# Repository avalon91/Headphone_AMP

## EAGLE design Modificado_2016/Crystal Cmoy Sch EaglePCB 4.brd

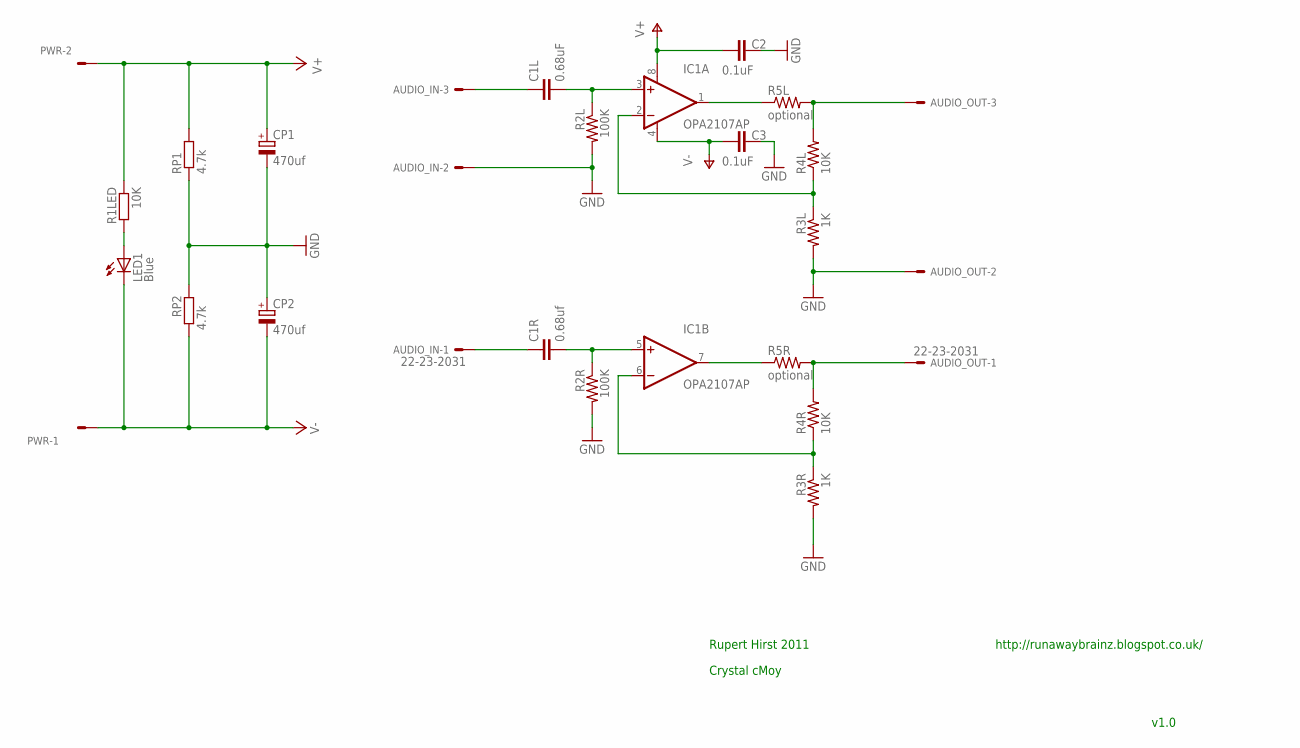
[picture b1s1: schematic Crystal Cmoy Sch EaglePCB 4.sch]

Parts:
AUDIO_IN: 22-23-2031
AUDIO_OUT: 22-23-2031
C1L: 0.68uF; C15B7
C1R: 0.68uf; C15B7
C2: 0.1uF; C5B2.5
C3: 0.1uF; C5B5.5
CP1, CP2: 470uf; E5-13
IC1: OPA2107AP; DIL08
LED1: Blue; LED3MM
PWR: 22-23-2021
R1LED: 10K; 0207/2V
R2L, R2R: 100K; 0207/10
R3L, R3R: 1K; 0207/10
R4L, R4R: 10K; 0207/10
R5L, R5R: optional; 0207/10
RP1, RP2: 4.7k; 0207/10

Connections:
GND: AUDIO_IN.2, AUDIO_OUT.2, C2.1, C3.2, CP1.-, CP2.+, R2L.2, R2R.2, R3L.2, R3R.2, RP1.1, RP2.2
L-IN: AUDIO_IN.3, C1L.1
L-OUT: AUDIO_OUT.3, R4L.2, R5L.2
unnamed: IC1.1 (OUT), R5L.1
unnamed: IC1.2 (-IN), R3L.1, R4L.1
unnamed: C1L.2, IC1.3 (+IN), R2L.1
unnamed: IC1.7 (OUT), R5R.1
unnamed: IC1.6 (-IN), R3R.1, R4R.1
unnamed: C1R.2, IC1.5 (+IN), R2R.1
unnamed: LED1.A, R1LED.2
R-IN: AUDIO_IN.1, C1R.1
R-OUT: AUDIO_OUT.1, R4R.2, R5R.2
V+: C2.2, CP1.+, IC1.8 (V+), PWR.2, R1LED.1, RP1.2
V-: C3.1, CP2.-, IC1.4 (V-), LED1.K (C), PWR.1, RP2.1

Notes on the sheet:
Rupert Hirst 2011
http://runawaybrainz.blogspot.co.uk/
Crystal cMoy
v1.0

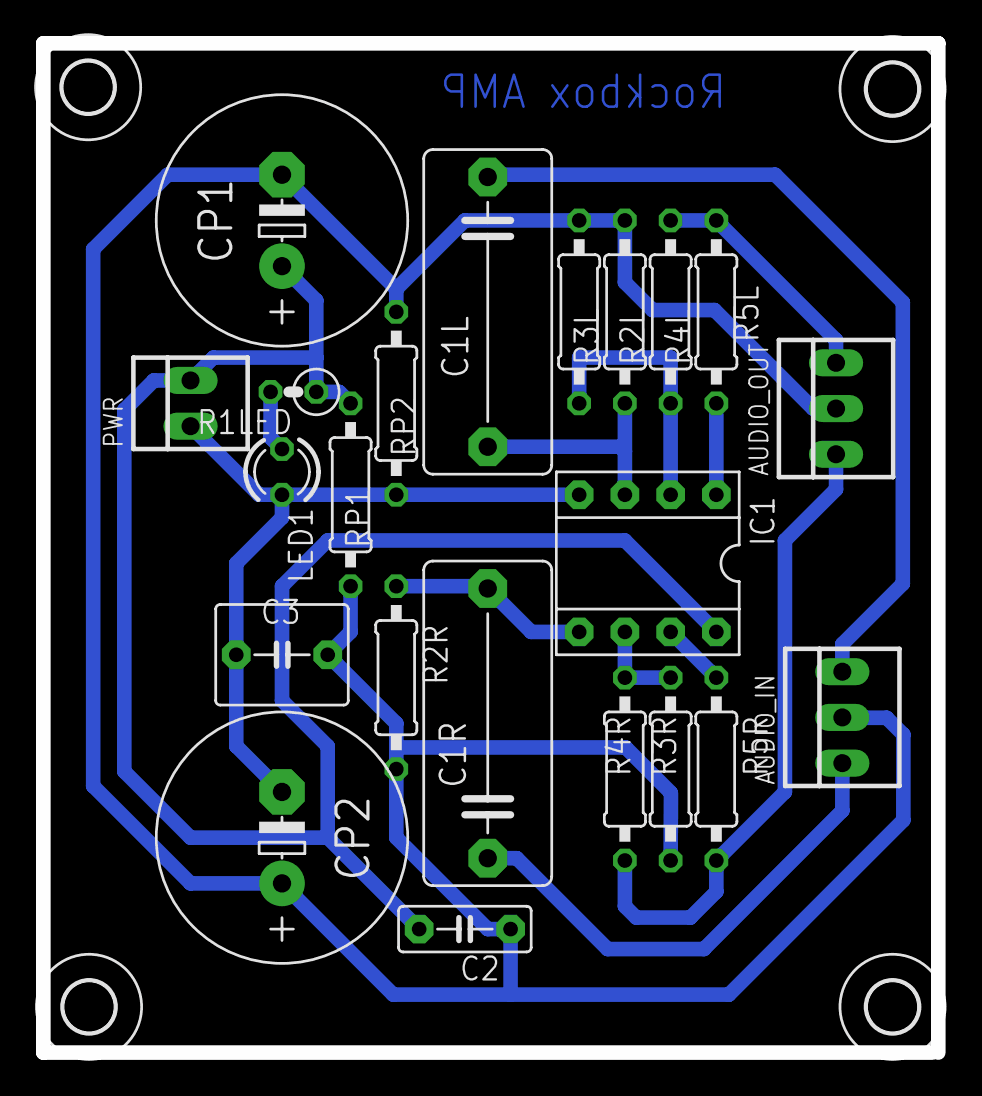
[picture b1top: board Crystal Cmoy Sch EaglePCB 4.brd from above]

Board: 2 copper layers, 49.7 x 56.1 mm, 26 parts (0 on the bottom side), 14 nets.

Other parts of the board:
U$1, U$2, U$3, U$4: 2,8

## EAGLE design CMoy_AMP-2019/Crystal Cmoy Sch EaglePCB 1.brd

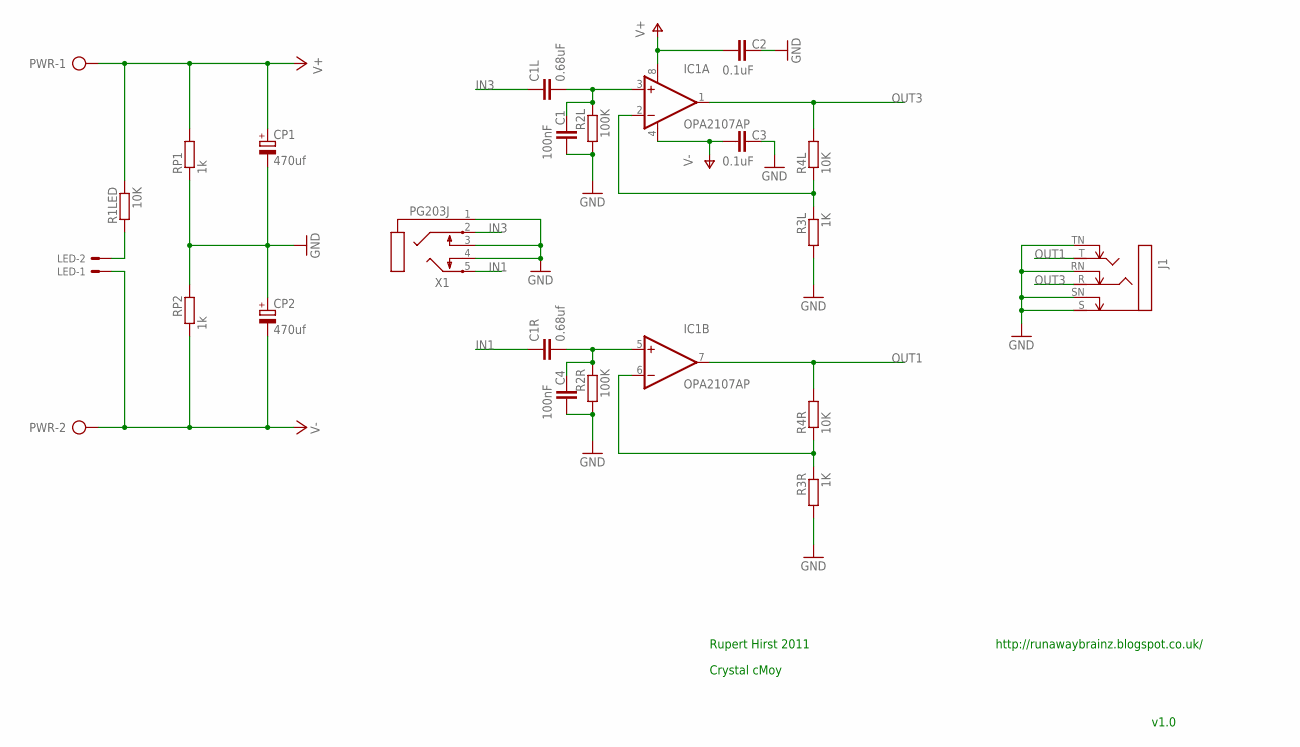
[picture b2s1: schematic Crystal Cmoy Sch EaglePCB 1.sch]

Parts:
C1, C4: 100nF; C025-025X050
C1L: 0.68uF; C5B4.5
C1R: 0.68uf; C5B4.5
C2, C3: 0.1uF; C5B2.5
CP1, CP2: 470uf; E5-13
IC1: OPA2107AP; DIL08
J1: STEREOSW; NMJ6HCD2
LED: 22-23-2021
PWR: AK500/2
R1LED, R4L, R4R: 10K; 0411/15
R2L, R2R: 100K; 0411/15
R3L, R3R: 1K; 0411/15
RP1, RP2: 1k; 0411/15
X1: PG203J

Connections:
GND: C1.2, C2.1, C3.1, C4.2, CP1.-, CP2.+, J1.RN, J1.S, J1.SN, J1.TN, R2L.2, R2R.2, R3L.2, R3R.2, RP1.1, RP2.2, X1.1, X1.3, X1.4
IN1: C1R.1, X1.5
IN3: C1L.1, X1.2
unnamed: IC1.2 (-IN), R3L.1, R4L.1
unnamed: C1.1, C1L.2, IC1.3 (+IN), R2L.1
unnamed: IC1.6 (-IN), R3R.1, R4R.1
unnamed: C1R.2, C4.1, IC1.5 (+IN), R2R.1
unnamed: LED.2, R1LED.2
OUT1: IC1.7 (OUT), J1.T, R4R.2
OUT3: IC1.1 (OUT), J1.R, R4L.2
V+: C2.2, CP1.+, IC1.8 (V+), PWR.1, R1LED.1, RP1.2
V-: C3.2, CP2.-, IC1.4 (V-), LED.1, PWR.2, RP2.1

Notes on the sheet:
Rupert Hirst 2011
http://runawaybrainz.blogspot.co.uk/
Crystal cMoy
v1.0

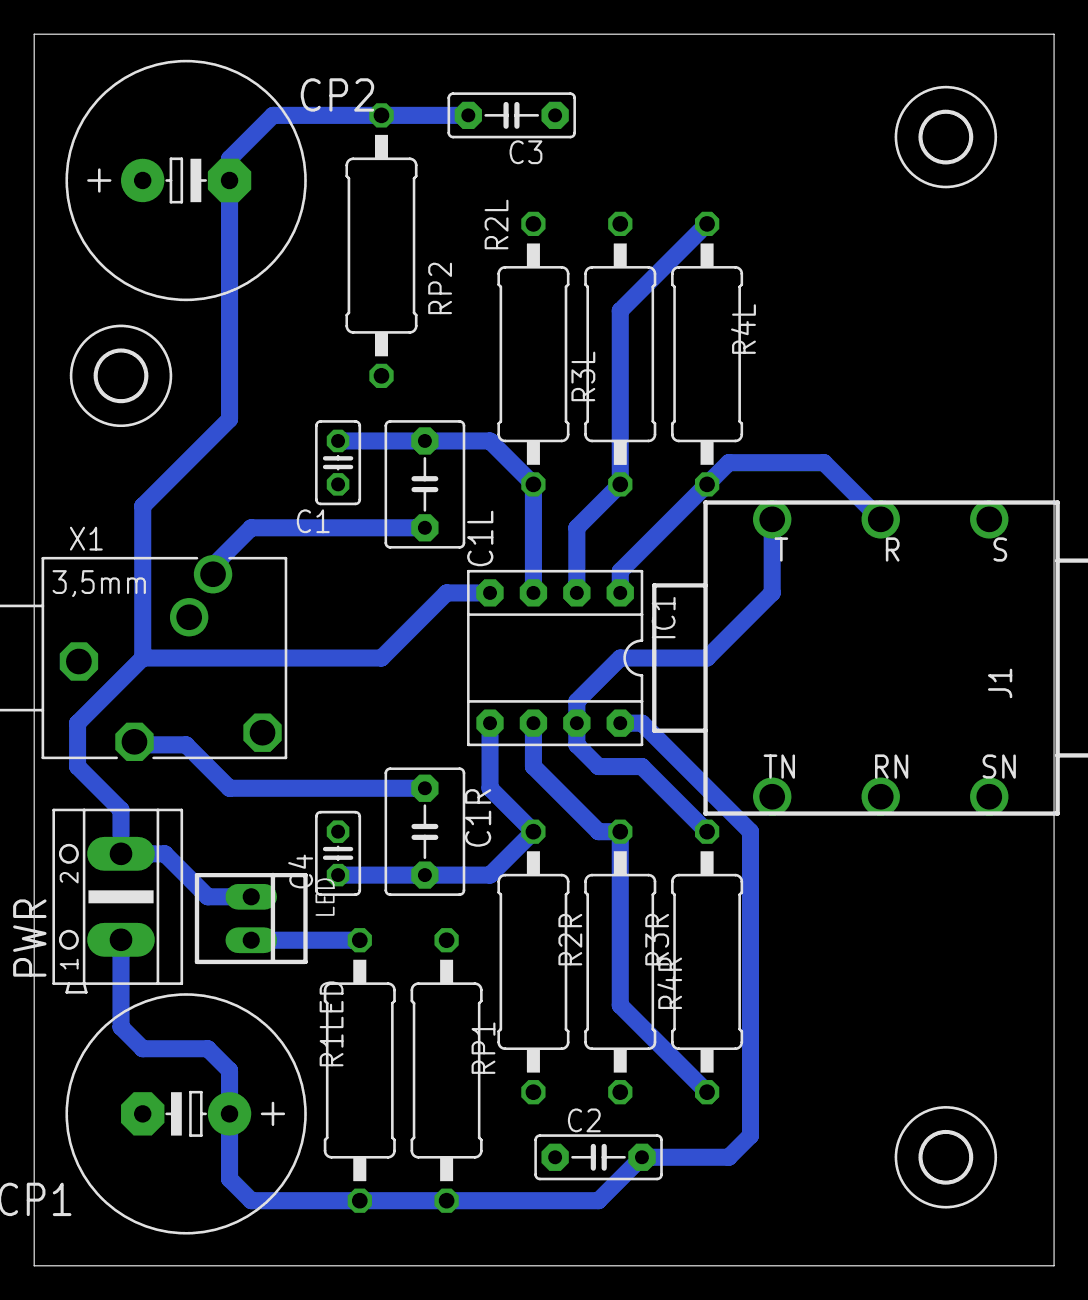
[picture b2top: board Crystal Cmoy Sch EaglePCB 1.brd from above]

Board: 2 copper layers, 59.7 x 72.1 mm, 25 parts (0 on the bottom side), 12 nets.

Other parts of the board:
U$1, U$2, U$3: 2,8

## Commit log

2016-05-02 :octocat: Added .gitattributes & .gitignore files
2016-05-02 Inserção de arquivos
    Pasta com meu desenho de PCB (possivelmente ruim) e pasta com arquivos
    potencialmente originais
2016-05-09 Novo desenho
    Leves modificações + adição de 4 centímetros de borda
2019-11-13 Add modificações 2016 + versão 2019
